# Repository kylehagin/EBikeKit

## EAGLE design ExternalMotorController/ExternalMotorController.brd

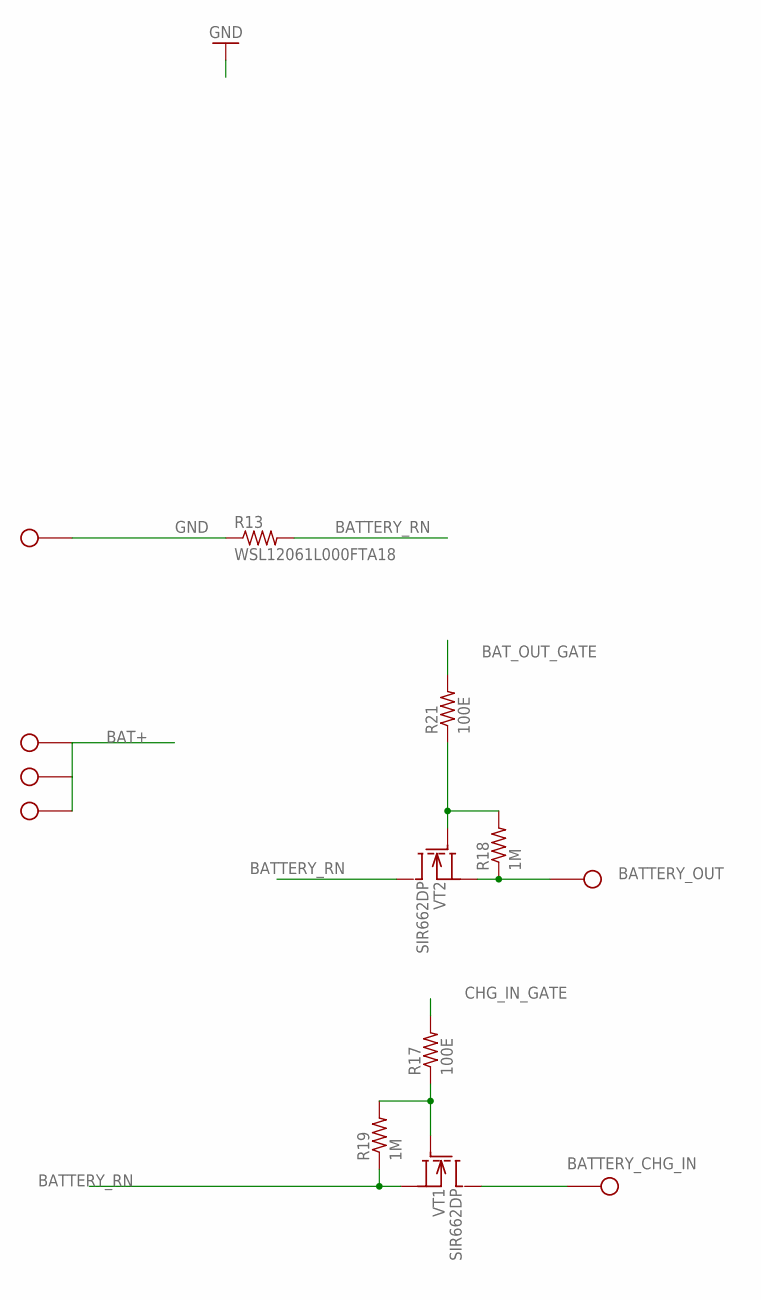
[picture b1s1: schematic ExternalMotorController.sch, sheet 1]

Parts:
R13: WSL12061L000FTA18; R2512
R17, R21: 100E; R0402
R18, R19: 1M; R0402
VT1, VT2: SIR662DP; POWERPAK_SO8
X1, X2, X3, X4, X5, X13: SOLDER_HOLE18AWG; SOLDER_HOLE_18

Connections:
BAT+: X1.1, X4.1, X5.1; also elsewhere on the board
BATTERY_CHG_IN: VT1.D, X2.1
BATTERY_OUT: R18.1, VT2.S1 (S), VT2.S2 (S), VT2.S3 (S), X3.1; also elsewhere on the board
BATTERY_RN: R13.2, R19.1, VT1.S1 (S), VT1.S2 (S), VT1.S3 (S), VT2.D; also elsewhere on the board
BAT_OUT_GATE: R21.2; also elsewhere on the board
CHG_IN_GATE: R17.2; also elsewhere on the board
GND: R13.1, X13.1; also elsewhere on the board
unnamed: R18.2, R21.1, VT2.G
unnamed: R17.1, R19.2, VT1.G

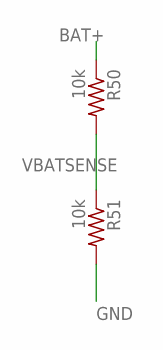
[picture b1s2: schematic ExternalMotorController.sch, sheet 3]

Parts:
R50, R51: 10k; R0402

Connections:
BAT+: R50.1; also elsewhere on the board
GND: R51.2; also elsewhere on the board
VBATSENSE: R50.2, R51.1; also elsewhere on the board

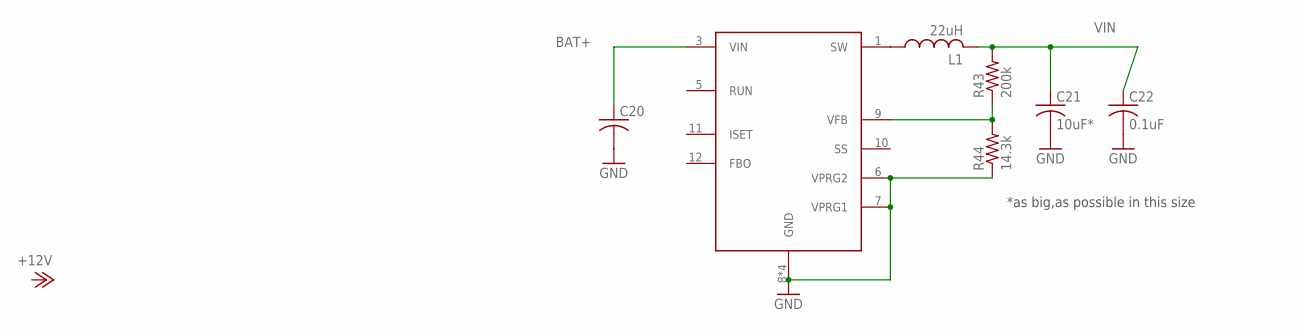
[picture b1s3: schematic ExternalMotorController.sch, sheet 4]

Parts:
C20: RCL_C-USC0805; RCL_C0805$1
C21: 10uF*; RCL_C4532$1
C22: 0.1uF; C0402
DA2: LTC3630; MSE16(12)
L1: 22uH; M-PAD-2.1_1210
R43: 200k; RCL_R0402
R44: 14.3k; RCL_R0402

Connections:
BAT+: C20.1, DA2.3 (VIN); also elsewhere on the board
GND: C20.2, C21.2, C22.2, DA2.6 (VPRG2), DA2.7 (VPRG1), DA2.8 (GND), DA2.14 (GND), DA2.16 (GND), DA2.17 (GND), R44.1; also elsewhere on the board
unnamed: DA2.1 (SW), L1.1
unnamed: DA2.9 (VFB), R43.1, R44.2
VIN: C21.1, C22.1, L1.2, R43.2; also elsewhere on the board

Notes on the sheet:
*as big,as possible in this size

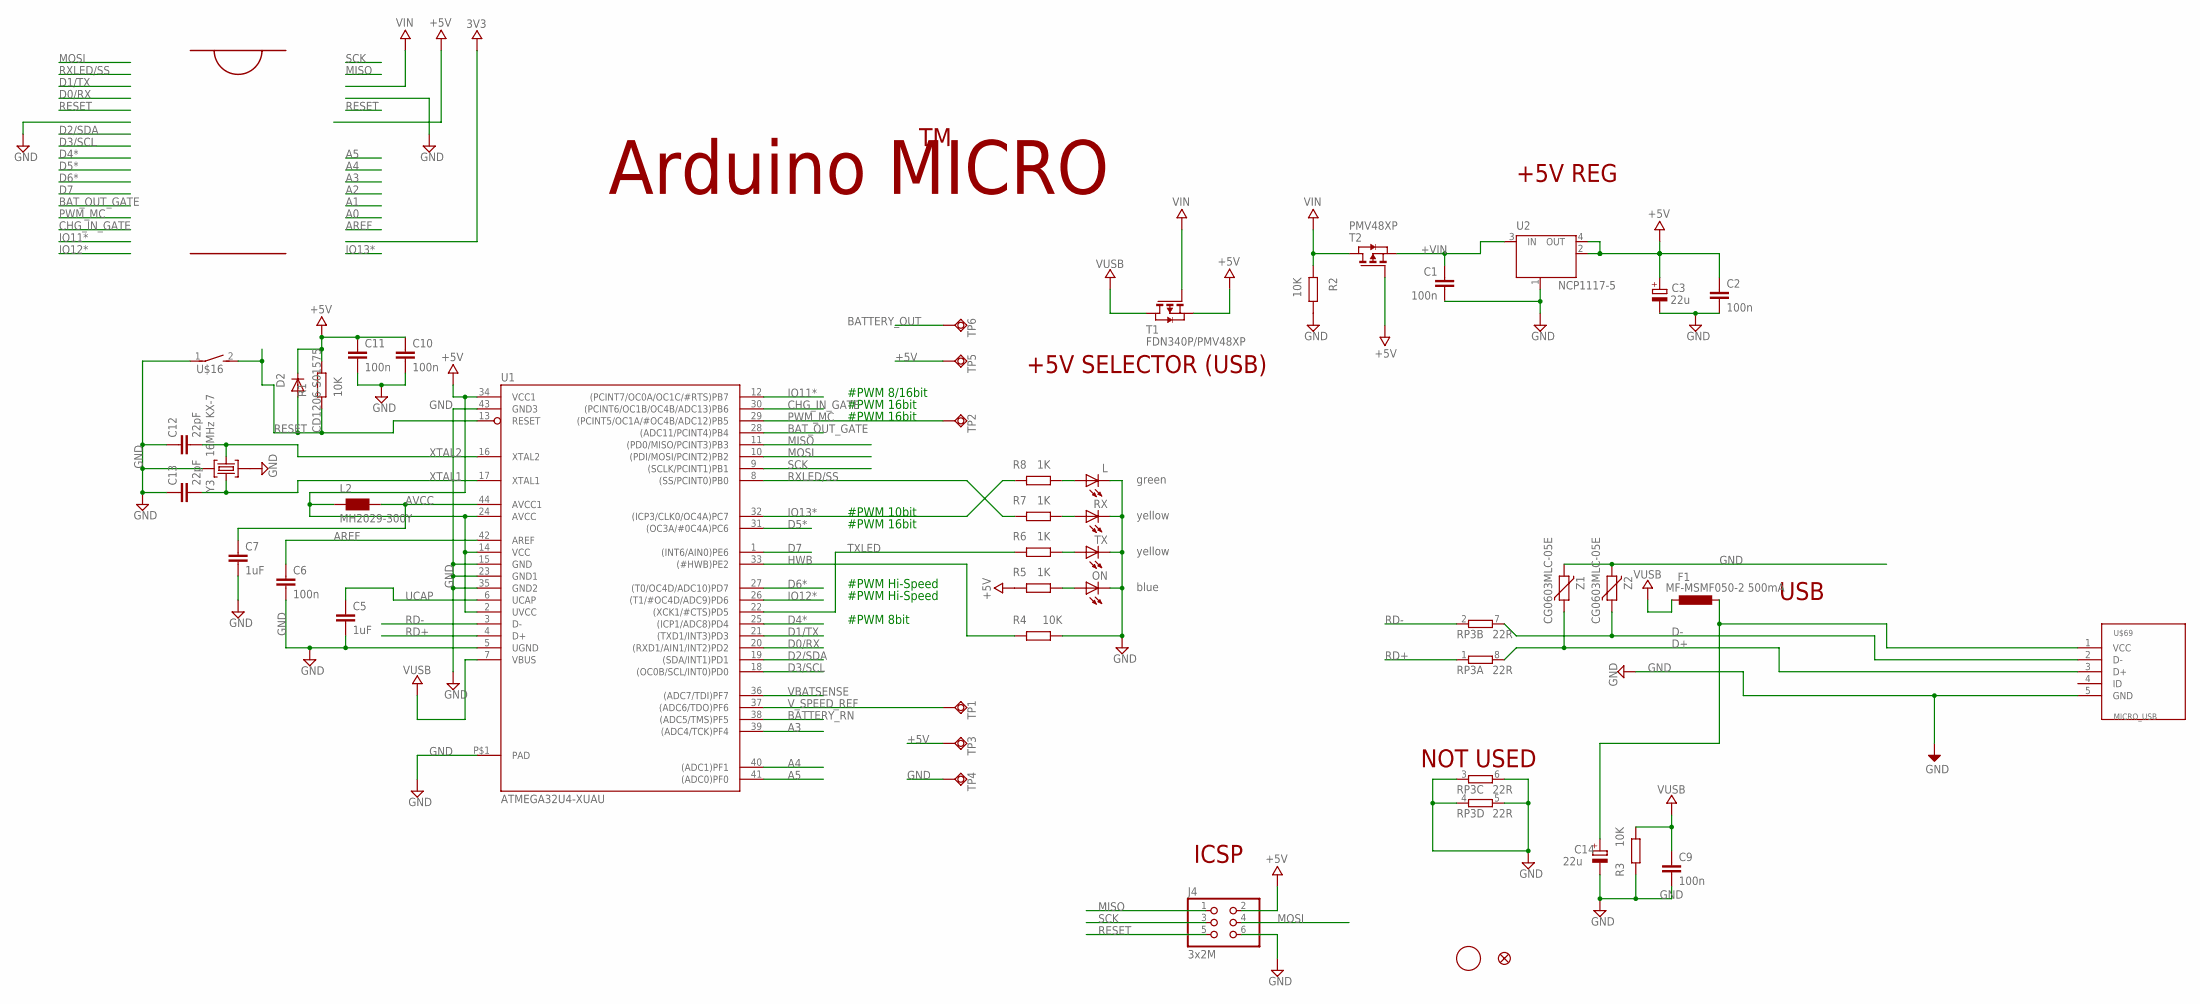
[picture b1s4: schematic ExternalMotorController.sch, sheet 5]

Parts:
C1, C2, C6, C9, C10, C11: 100n; C0402
C3, C14: 22u; SMC_B
C5, C7: 1uF; C0402
C12, C13: 22pF; C0402
D2: CD1206-S01575; MINIMELF
F1: MF-MSMF050-2 500mA; L1812
J4: 3x2M; 2X03
L: green; CHIPLED_0805
L2: MH2029-300Y; 0805
ON: blue; CHIPLED_0805
R1, R2, R3, R4: 10K; R0402
R5, R6, R7, R8: 1K; R0402
RP3: 22R; CAY16
RX: yellow; CHIPLED_0805
T1: FDN340P/PMV48XP; SOT-23
T2: PMV48XP; SOT-23
TP1, TP2, TP3, TP4, TP5, TP6: TPSQTP15SQ; TP15SQ
TX: yellow; CHIPLED_0805
U1: ATMEGA32U4-XUAU; TQFP44-PAD
U2: NCP1117-5; LINEAR_SOT223
U$16: RGHT-ANGLE-SMT-SWITCH-688-SKRELF; 2.9X3.9X2.0
U$37: FIDUCIALMOUNT; FIDUCIA-MOUNT
U$53: FIDUCIAL1X2; FIDUCIAL-1X2
U$69: MICRO_USB
Y3: 16MHz KX-7; CRYSTAL-3.2-2.5
Z1, Z2: CG0603MLC-05E; CT/CN0603

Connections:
+5V: C2.1, C3.+, C10.1, C11.1, D2.C, J4.2, L2.1, R1.1, R5.1, T1.2 (S), T2.3 (G), TP3.TP, TP5.TP, U1.2 (UVCC), U1.14 (VCC), U1.24 (AVCC), U1.34 (VCC1), U2.2 (OUT), U2.4 (OUT)
+VIN: C1.1, T2.2 (S), U2.3 (IN)
A3: U1.39 ((ADC4/TCK)PF4)
A4: U1.40 ((ADC1)PF1)
A5: U1.41 ((ADC0)PF0)
AREF: C6.1, U1.42 (AREF)
AVCC: C7.1, L2.2, U1.44 (AVCC1)
BATTERY_OUT: TP6.TP; also elsewhere on the board
BATTERY_RN: U1.38 ((ADC5/TMS)PF5); also elsewhere on the board
BAT_OUT_GATE: U1.28 ((ADC11/PCINT4)PB4); also elsewhere on the board
CHG_IN_GATE: U1.30 ((PCINT6/OC1B/OC4B/ADC13)PB6); also elsewhere on the board
D0/RX: U1.20 ((RXD1/AIN1/INT2)PD2)
D1/TX: U1.21 ((TXD1/INT3)PD3)
D2/SDA: U1.19 ((SDA/INT1)PD1)
D3/SCL: U1.18 ((OC0B/SCL/INT0)PD0)
D4*: U1.25 ((ICP1/ADC8)PD4)
D5*: U1.31 ((OC3A/#0C4A)PC6)
D6*: U1.27 ((T0/OC4D/ADC10)PD7)
D7: U1.1 ((INT6/AIN0)PE6)
D+: RP3.8 (2), U$69.3 (D+), Z1.1
D-: RP3.7 (2), U$69.2 (D-), Z2.1
GND: C1.2, C2.2, C3.-, C5.2, C6.2, C7.2, C9.2, C10.2, C11.2, C12.1, C13.1, C14.-, J4.6, L.C, ON.C, R2.1, R3.1, R4.2, RP3.3 (1), RP3.4 (1), RP3.5 (2), RP3.6 (2), RX.C, TP4.TP, TX.C, U1.5 (UGND), U1.15 (GND), U1.23 (GND1), U1.35 (GND2), U1.43 (GND3), U1.P$1 (PAD), U2.1 (GND/ADJ), U$16.1, U$69.5 (GND), Y3.2 (GND), Y3.4 (GND), Z1.2, Z2.2; also elsewhere on the board
HWB: R4.1, U1.33 ((#HWB)PE2)
IO11*: U1.12 ((PCINT7/OC0A/OC1C/#RTS)PB7)
IO12*: U1.26 ((T1/#OC4D/ADC9)PD6)
IO13*: R8.1, U1.32 ((ICP3/CLK0/OC4A)PC7)
MISO: J4.1, U1.11 ((PD0/MISO/PCINT3)PB3)
MOSI: J4.4, U1.10 ((PDI/MOSI/PCINT2)PB2)
unnamed: R7.2, RX.A
unnamed: ON.A, R5.2
unnamed: R6.2, TX.A
unnamed: L.A, R8.2
PWM_MC: TP2.TP, U1.29 ((PCINT5/OC1A/#OC4B/ADC12)PB5)
RD+: RP3.1, U1.4 (D+)
RD-: RP3.2 (1), U1.3 (D-)
RESET: D2.A, J4.5, R1.2, U1.13 (RESET), U$16.2
RXLED/SS: R7.1, U1.8 ((SS/PCINT0)PB0)
SCK: J4.3, U1.9 ((SCLK/PCINT1)PB1)
TXLED: R6.1, U1.22 ((XCK1/#CTS)PD5)
UCAP: C5.1, U1.6 (UCAP)
VBATSENSE: U1.36 ((ADC7/TDI)PF7); also elsewhere on the board
VIN: R2.2, T1.3 (G), T2.1 (D); also elsewhere on the board
VUSB: C9.1, F1.2, R3.2, T1.1 (D), U1.7 (VBUS)
VUSBD: C14.+, F1.1, U$69.1 (VCC)
V_SPEED_REF: TP1.TP, U1.37 ((ADC6/TDO)PF6)
XTAL1: C13.2, U1.17 (XTAL1), Y3.3 (C2)
XTAL2: C12.2, U1.16 (XTAL2), Y3.1 (C1)

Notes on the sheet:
Arduino MICRO
+5V REG
ICSP
USB
+5V SELECTOR (USB)
NOT USED
#PWM 8bit
#PWM Hi-Speed
#PWM 16bit
#PWM 10bit
#PWM 8/16bit

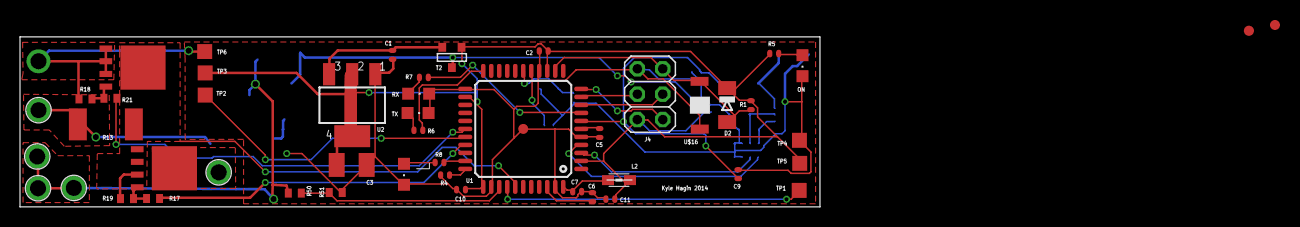
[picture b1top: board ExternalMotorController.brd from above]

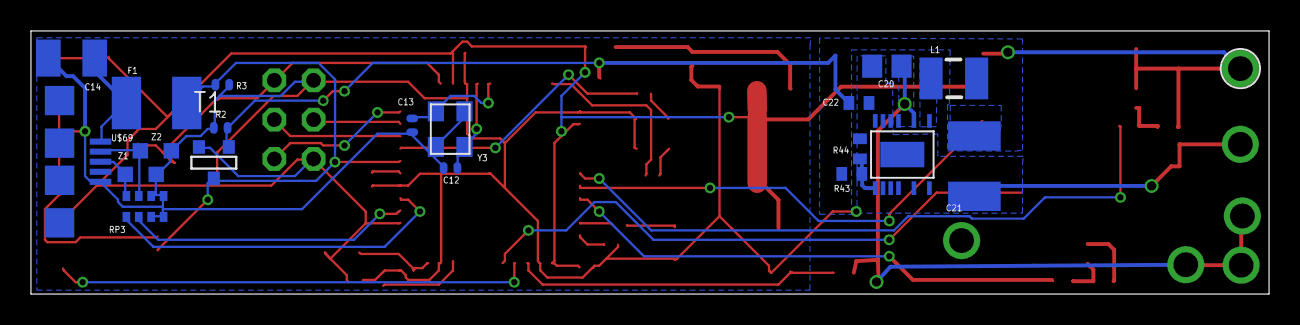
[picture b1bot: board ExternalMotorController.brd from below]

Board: 2 copper layers, 80.0 x 17.0 mm, 68 parts (20 on the bottom side), 40 nets.

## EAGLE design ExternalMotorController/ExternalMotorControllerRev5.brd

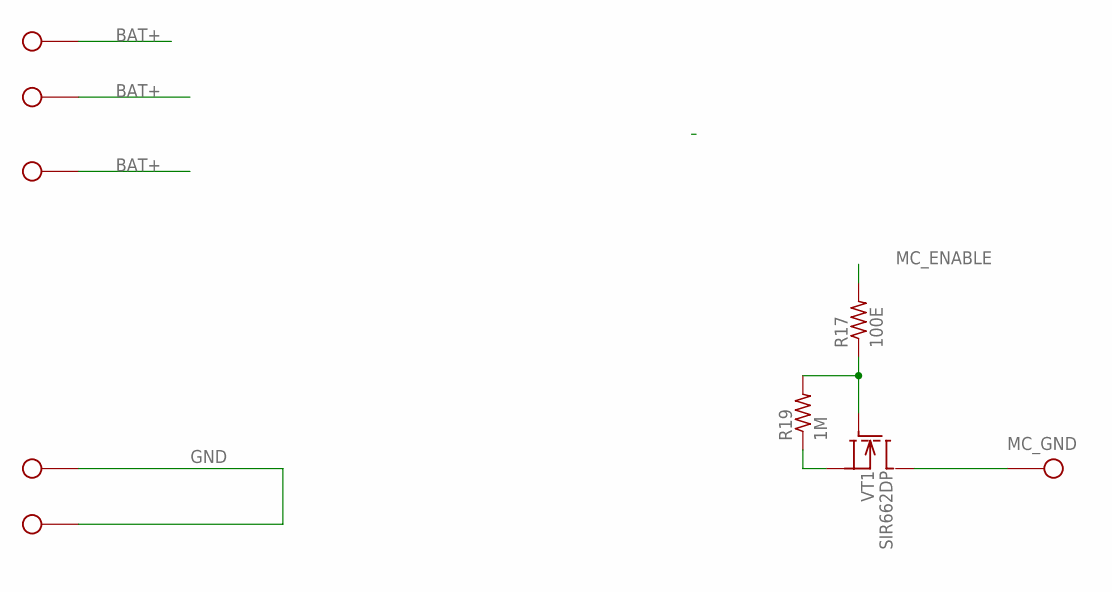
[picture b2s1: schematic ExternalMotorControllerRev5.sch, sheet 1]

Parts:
R17: 100E; R0402
R19: 1M; R0402
VT1: SIR662DP; POWERPAK_SO8
X1, X2, X3, X4, X5, X13: SOLDER_HOLE18AWG; SOLDER_HOLE_18

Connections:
BAT+: X1.1, X3.1, X4.1; also elsewhere on the board
GND: R19.1, VT1.S1 (S), VT1.S2 (S), VT1.S3 (S), X5.1, X13.1; also elsewhere on the board
MC_ENABLE: R17.2; also elsewhere on the board
MC_GND: VT1.D, X2.1; also elsewhere on the board
unnamed: R17.1, R19.2, VT1.G

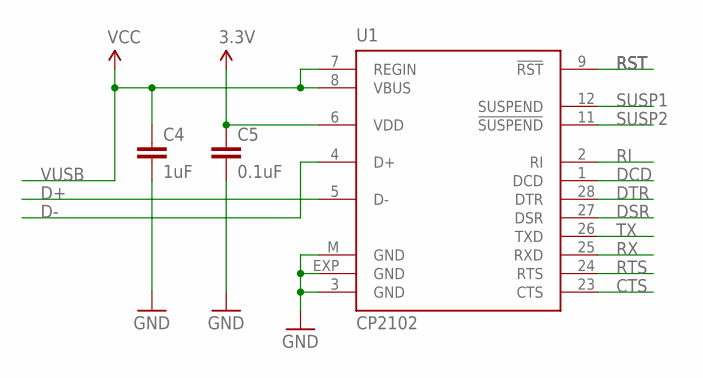
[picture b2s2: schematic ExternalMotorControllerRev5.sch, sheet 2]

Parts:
C4: 1uF; C0402
C5: 0.1uF; C0402
U1: CP2102; MLP28

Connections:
3.3V: C5.1, U1.6 (VDD)
CTS: U1.23 (CTS)
D+: U1.5 (D-)
D-: U1.4 (D+)
DCD: U1.1 (DCD)
DSR: U1.27 (DSR)
DTR: U1.28 (DTR); also elsewhere on the board
GND: C4.2, C5.2, U1.3 (GND), U1.EXP (GND), U1.M (GND); also elsewhere on the board
RI: U1.2 (RI)
RST: U1.9 (!RST)
RTS: U1.24 (RTS)
RX: U1.25 (RXD); also elsewhere on the board
SUSP1: U1.12 (SUSPEND)
SUSP2: U1.11 (!SUSPEND)
TX: U1.26 (TXD); also elsewhere on the board
VUSB: C4.1, U1.7 (REGIN), U1.8 (VBUS); also elsewhere on the board

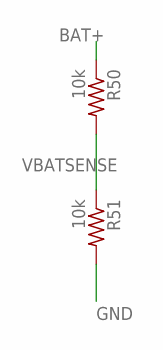
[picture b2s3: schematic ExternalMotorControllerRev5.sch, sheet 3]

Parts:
R50, R51: 10k; R0402

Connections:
BAT+: R50.1; also elsewhere on the board
GND: R51.2; also elsewhere on the board
VBATSENSE: R50.2, R51.1; also elsewhere on the board

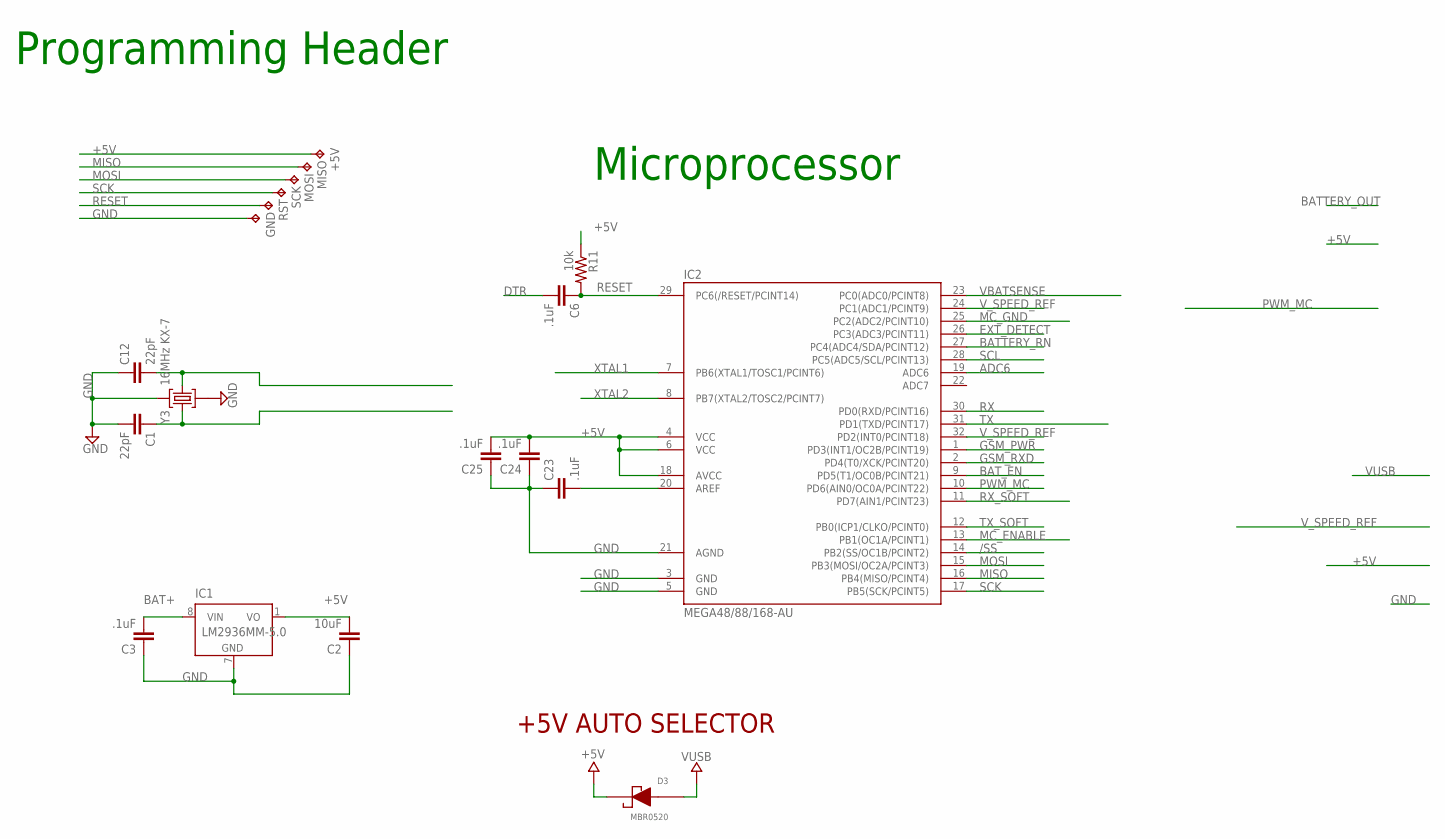
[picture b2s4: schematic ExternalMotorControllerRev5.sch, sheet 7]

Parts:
+5V: TPTP08R; TP08R
C1, C12: 22pF; C0402
C2: 10uF; C0805
C3, C6, C23, C24, C25: .1uF; C0402
D3: MBR0520; SOD-123
GND: TPTP10R; TP10R
IC1: LM2936MM-5.0; MINI-SO8
IC2: MEGA48/88/168-AU; TQFP32-08
MISO: TPTP08R; TP08R
MOSI: TPTP08R; TP08R
R11: 10k; R0402
RST: TPTP10R; TP10R
SCK: TPTP08R; TP08R
Y3: 16MHz KX-7; CRYSTAL-3.2-2.5

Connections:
+5V: +5V.TP, C2.2, C24.2, C25.2, D3.1 (CA), IC1.1 (VO), IC2.4 (VCC), IC2.6 (VCC), IC2.18 (AVCC), R11.1
/SS: IC2.14 (PB2(SS/OC1B/PCINT2))
ADC6: IC2.19 (ADC6)
BAT+: C3.2, IC1.8 (VIN); also elsewhere on the board
BATTERY_RN: IC2.27 (PC4(ADC4/SDA/PCINT12))
BAT_EN: IC2.9 (PD5(T1/OC0B/PCINT21))
DTR: C6.2; also elsewhere on the board
EXT_DETECT: IC2.26 (PC3(ADC3/PCINT11))
GND: C1.2, C2.1, C3.1, C12.1, C23.1, C24.1, C25.1, GND.TP, IC1.7 (GND), IC2.3 (GND), IC2.5 (GND), IC2.21 (AGND), Y3.2 (GND), Y3.4 (GND); also elsewhere on the board
GSM_PWR: IC2.1 (PD3(INT1/OC2B/PCINT19))
GSM_RXD: IC2.2 (PD4(T0/XCK/PCINT20))
MC_ENABLE: IC2.13 (PB1(OC1A/PCINT1)); also elsewhere on the board
MC_GND: IC2.25 (PC2(ADC2/PCINT10)); also elsewhere on the board
MISO: IC2.16 (PB4(MISO/PCINT4)), MISO.TP
MOSI: IC2.15 (PB3(MOSI/OC2A/PCINT3)), MOSI.TP
unnamed: C23.2, IC2.20 (AREF)
PWM_MC: IC2.10 (PD6(AIN0/OC0A/PCINT22))
RESET: C6.1, IC2.29 (PC6(/RESET/PCINT14)), R11.2, RST.TP
RX: IC2.30 (PD0(RXD/PCINT16)); also elsewhere on the board
RX_SOFT: IC2.11 (PD7(AIN1/PCINT23))
SCK: IC2.17 (PB5(SCK/PCINT5)), SCK.TP
SCL: IC2.28 (PC5(ADC5/SCL/PCINT13))
TX: IC2.31 (PD1(TXD/PCINT17)); also elsewhere on the board
TX_SOFT: IC2.12 (PB0(ICP1/CLKO/PCINT0))
VBATSENSE: IC2.23 (PC0(ADC0/PCINT8)); also elsewhere on the board
VUSB: D3.2 (AN); also elsewhere on the board
V_SPEED_REF: IC2.24 (PC1(ADC1/PCINT9)), IC2.32 (PD2(INT0/PCINT18))
XTAL1: C12.2, IC2.7 (PB6(XTAL1/TOSC1/PCINT6)), Y3.1 (C1)
XTAL2: C1.1, IC2.8 (PB7(XTAL2/TOSC2/PCINT7)), Y3.3 (C2)

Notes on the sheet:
Microprocessor
Programming Header
+5V AUTO SELECTOR

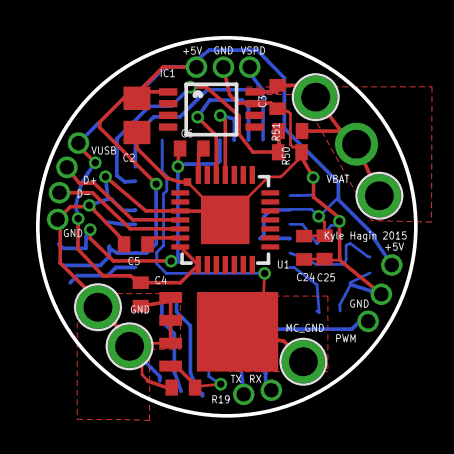
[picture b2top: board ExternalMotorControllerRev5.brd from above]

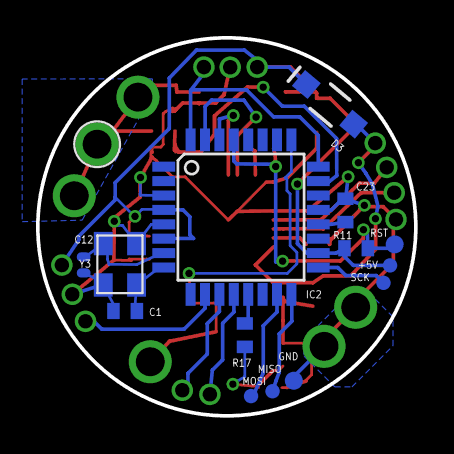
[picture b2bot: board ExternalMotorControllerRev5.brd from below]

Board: 2 copper layers, 21.0 x 21.0 mm, 33 parts (15 on the bottom side), 20 nets.

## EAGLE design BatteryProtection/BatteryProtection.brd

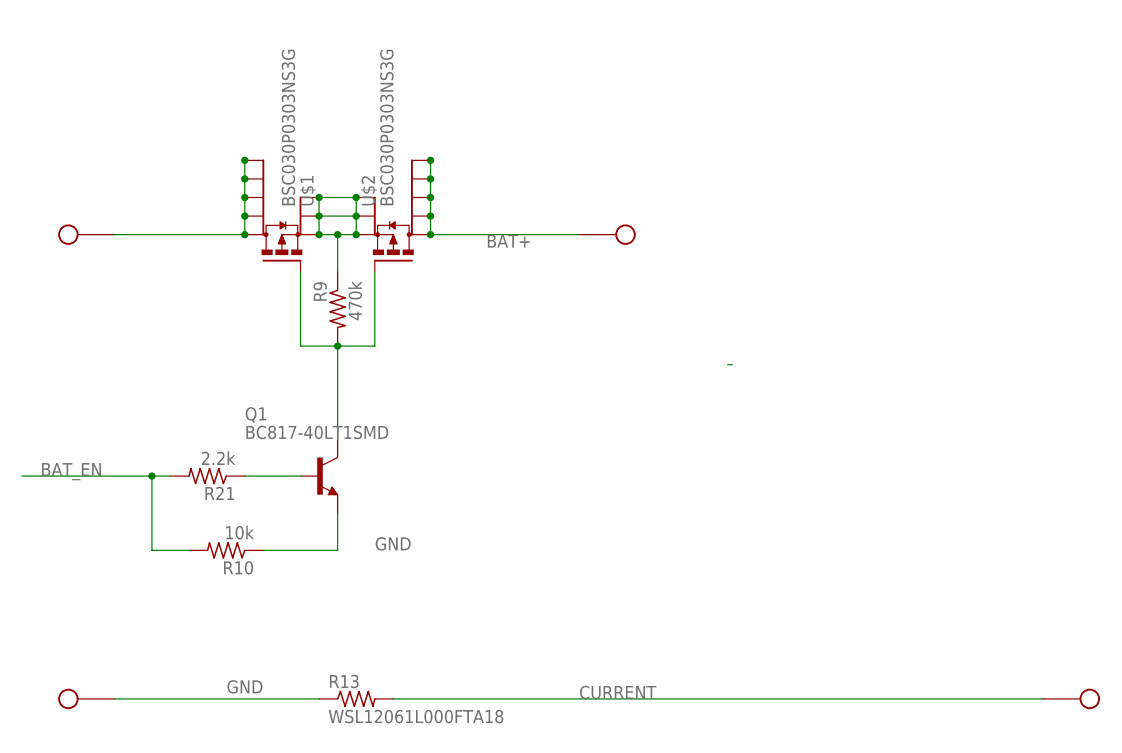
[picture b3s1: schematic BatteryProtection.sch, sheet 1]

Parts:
Q1: BC817-40LT1SMD; SOT23-BEC
R9: 470k; R0402
R10: 10k; R0402
R13: WSL12061L000FTA18; R2512
R21: 2.2k; R0402
U$1, U$2: BSC030P0303NS3G; PG-TDSON-8
X1, X2, X5, X13: SOLDER_HOLE18AWG; SOLDER_HOLE_18

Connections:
BAT+: U$2.5 (D), U$2.6 (D1), U$2.7 (D2), U$2.8 (D3), U$2.TH (D4), X1.1; also elsewhere on the board
BAT_EN: R10.2, R21.2; also elsewhere on the board
CURRENT: R13.2, X2.1; also elsewhere on the board
GND: Q1.E, R10.1, R13.1, X13.1; also elsewhere on the board
unnamed: R9.1, U$1.1 (S), U$1.2 (S1), U$1.3 (S2), U$2.1 (S), U$2.2 (S1), U$2.3 (S2)
unnamed: Q1.B, R21.1
unnamed: Q1.C, R9.2, U$1.4 (G), U$2.4 (G)
unnamed: U$1.5 (D), U$1.6 (D1), U$1.7 (D2), U$1.8 (D3), U$1.TH (D4), X5.1

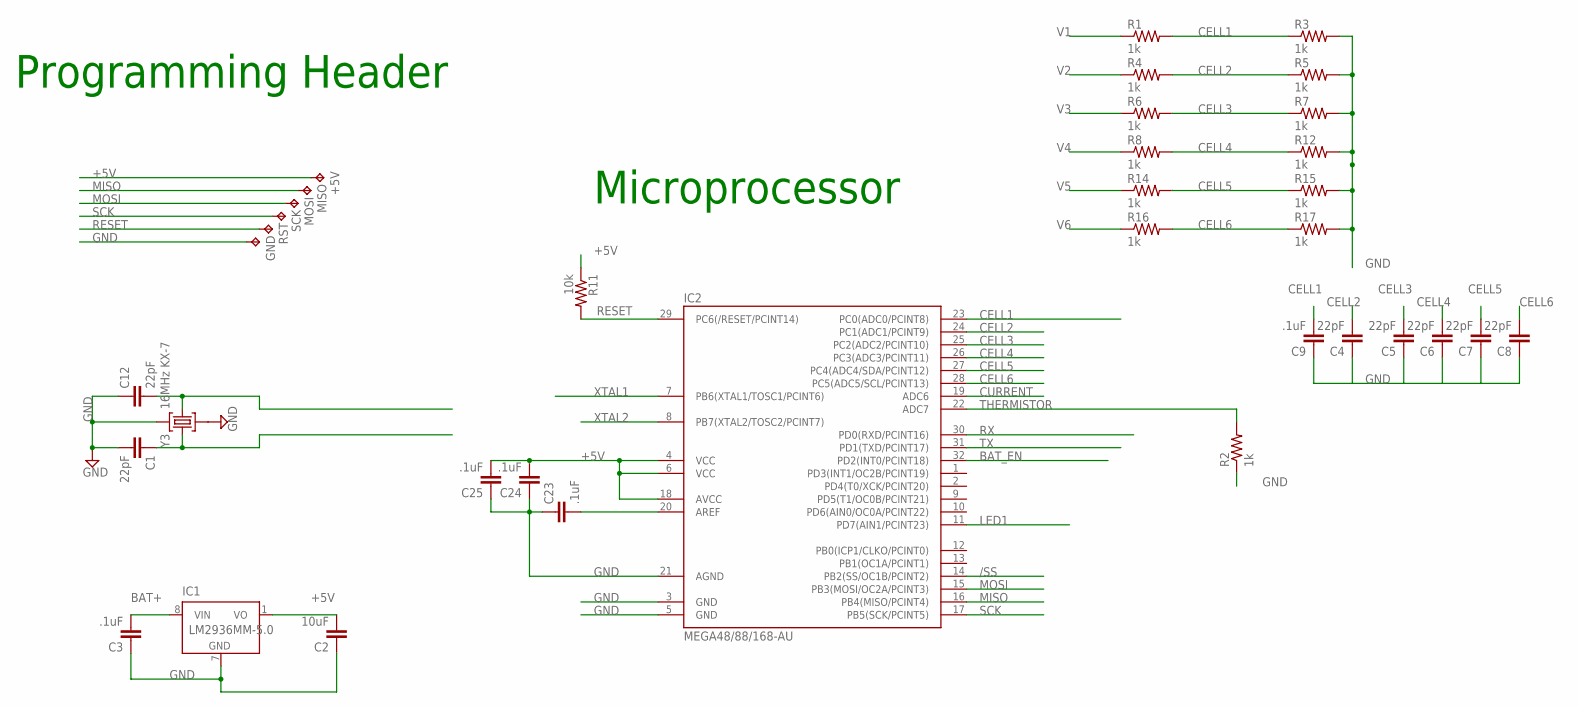
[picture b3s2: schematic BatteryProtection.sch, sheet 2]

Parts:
+5V: TPTP08R; TP08R
C1, C4, C5, C6, C7, C8, C12: 22pF; C0402
C2: 10uF; C0805
C3, C9, C23, C24, C25: .1uF; C0402
GND: TPTP08R; TP08R
IC1: LM2936MM-5.0; MINI-SO8
IC2: MEGA48/88/168-AU; TQFP32-08
MISO: TPTP08R; TP08R
MOSI: TPTP08R; TP08R
R1, R2, R3, R4, R5, R6, R7, R8, R12, R14, R15, R16, R17: 1k; R0402
R11: 10k; R0402
RST: TPTP08R; TP08R
SCK: TPTP08R; TP08R
Y3: 16MHz KX-7; CRYSTAL-3.2-2.5

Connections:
+5V: +5V.TP, C2.2, C24.2, C25.2, IC1.1 (VO), IC2.4 (VCC), IC2.6 (VCC), IC2.18 (AVCC), R11.1
/SS: IC2.14 (PB2(SS/OC1B/PCINT2))
BAT+: C3.2, IC1.8 (VIN); also elsewhere on the board
BAT_EN: IC2.32 (PD2(INT0/PCINT18)); also elsewhere on the board
CELL1: C9.2, IC2.23 (PC0(ADC0/PCINT8)), R1.2, R3.1
CELL2: C4.2, IC2.24 (PC1(ADC1/PCINT9)), R4.2, R5.1
CELL3: C5.2, IC2.25 (PC2(ADC2/PCINT10)), R6.2, R7.1
CELL4: C6.2, IC2.26 (PC3(ADC3/PCINT11)), R8.2, R12.1
CELL5: C7.2, IC2.27 (PC4(ADC4/SDA/PCINT12)), R14.2, R15.1
CELL6: C8.2, IC2.28 (PC5(ADC5/SCL/PCINT13)), R16.2, R17.1
CURRENT: IC2.19 (ADC6); also elsewhere on the board
GND: C1.2, C2.1, C3.1, C4.1, C5.1, C6.1, C7.1, C8.1, C9.1, C12.1, C23.1, C24.1, C25.1, GND.TP, IC1.7 (GND), IC2.3 (GND), IC2.5 (GND), IC2.21 (AGND), R2.1, R3.2, R5.2, R7.2, R12.2, R15.2, R17.2, Y3.2 (GND), Y3.4 (GND); also elsewhere on the board
LED1: IC2.11 (PD7(AIN1/PCINT23))
MISO: IC2.16 (PB4(MISO/PCINT4)), MISO.TP
MOSI: IC2.15 (PB3(MOSI/OC2A/PCINT3)), MOSI.TP
unnamed: C23.2, IC2.20 (AREF)
RESET: IC2.29 (PC6(/RESET/PCINT14)), R11.2, RST.TP
RX: IC2.30 (PD0(RXD/PCINT16))
SCK: IC2.17 (PB5(SCK/PCINT5)), SCK.TP
THERMISTOR: IC2.22 (ADC7), R2.2
TX: IC2.31 (PD1(TXD/PCINT17))
V1: R1.1
V2: R4.1
V3: R6.1
V4: R8.1
V5: R14.1
V6: R16.1
XTAL1: C1.1, IC2.7 (PB6(XTAL1/TOSC1/PCINT6)), Y3.3 (C2)
XTAL2: C12.2, IC2.8 (PB7(XTAL2/TOSC2/PCINT7)), Y3.1 (C1)

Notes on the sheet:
Microprocessor
Programming Header

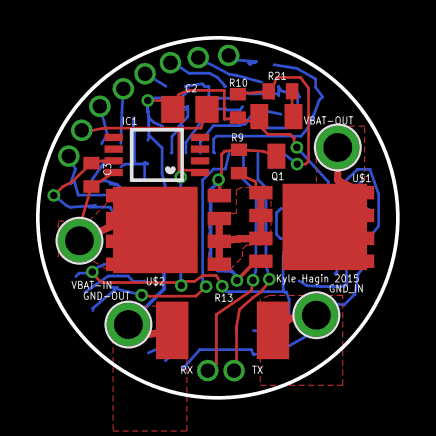
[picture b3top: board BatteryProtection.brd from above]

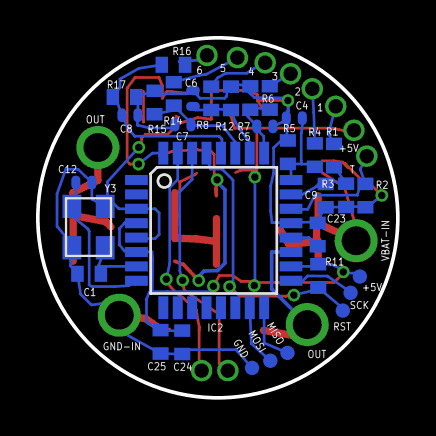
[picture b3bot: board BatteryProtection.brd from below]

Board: 2 copper layers, 20.0 x 20.0 mm, 47 parts (33 on the bottom side), 23 nets.

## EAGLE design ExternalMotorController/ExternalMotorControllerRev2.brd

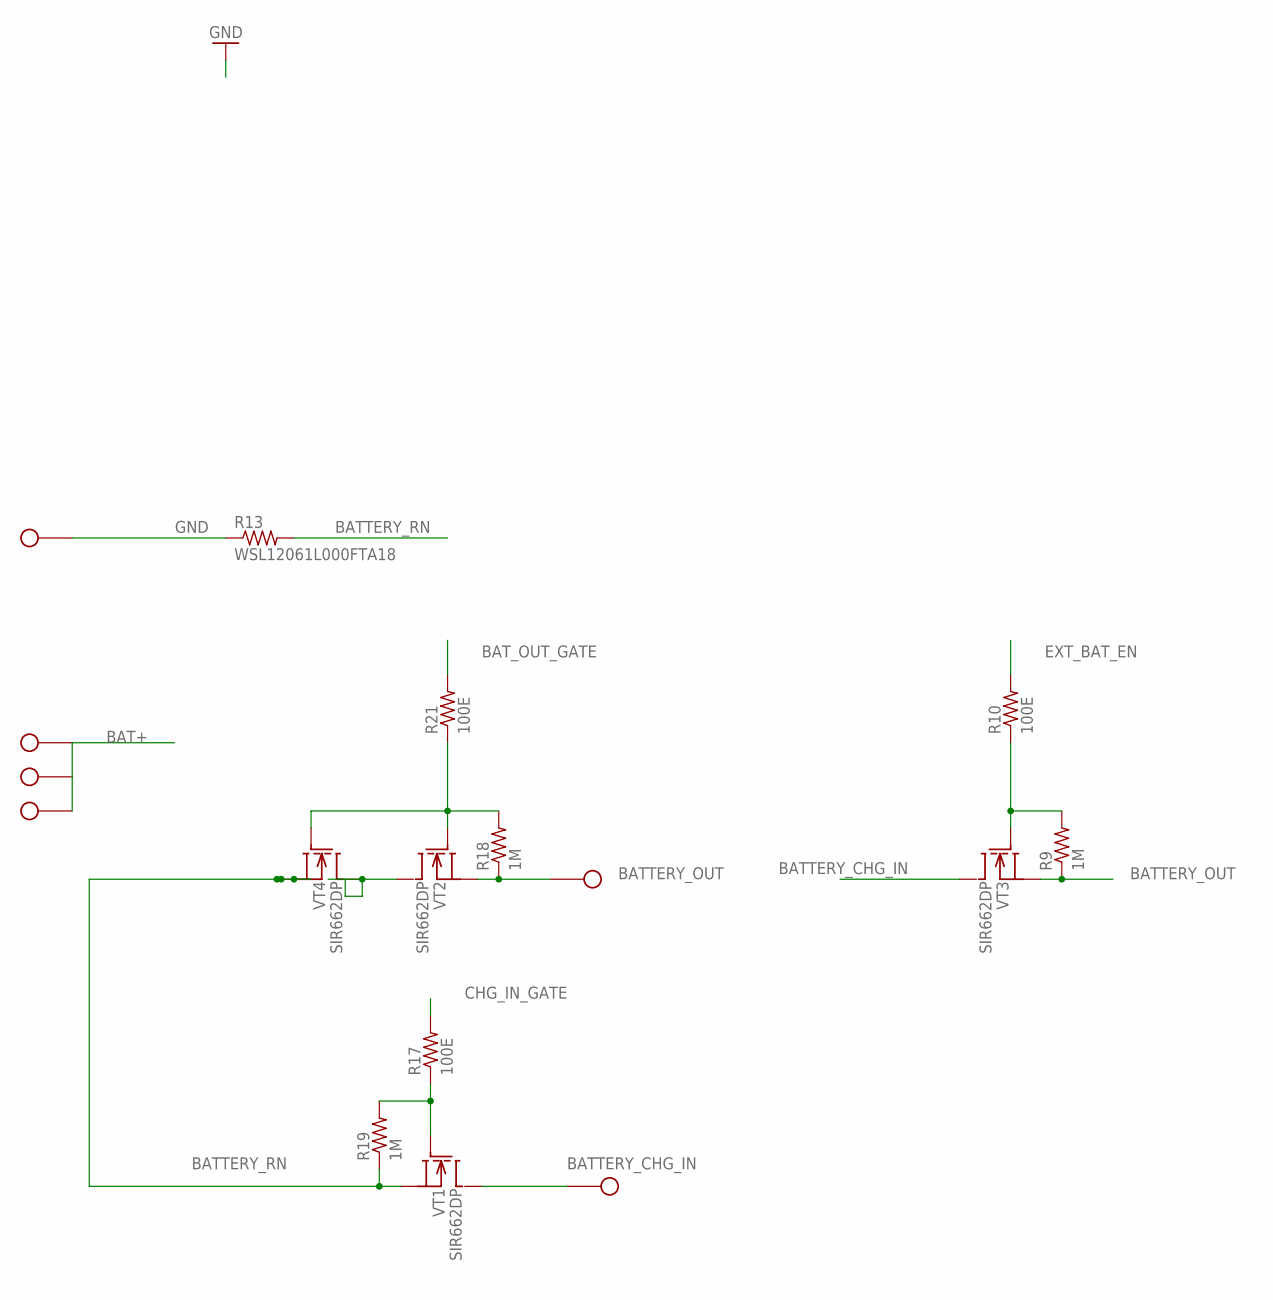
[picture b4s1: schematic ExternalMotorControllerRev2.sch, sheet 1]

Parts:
R9, R18, R19: 1M; R0402
R10, R17, R21: 100E; R0402
R13: WSL12061L000FTA18; R2512
VT1, VT2, VT3, VT4: SIR662DP; POWERPAK_SO8
X1, X2, X3, X4, X5, X13: SOLDER_HOLE18AWG; SOLDER_HOLE_18

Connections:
BAT+: X1.1, X4.1, X5.1; also elsewhere on the board
BATTERY_CHG_IN: VT1.D, VT3.D, X2.1
BATTERY_OUT: R9.1, R18.1, VT2.S1 (S), VT2.S2 (S), VT2.S3 (S), VT3.S1 (S), VT3.S2 (S), VT3.S3 (S), X3.1; also elsewhere on the board
BATTERY_RN: R13.2, R19.1, VT1.S1 (S), VT1.S2 (S), VT1.S3 (S), VT4.S1 (S), VT4.S2 (S), VT4.S3 (S); also elsewhere on the board
BAT_OUT_GATE: R21.2; also elsewhere on the board
CHG_IN_GATE: R17.2; also elsewhere on the board
EXT_BAT_EN: R10.2; also elsewhere on the board
GND: R13.1, X13.1; also elsewhere on the board
unnamed: R9.2, R10.1, VT3.G
unnamed: VT2.D, VT4.D
unnamed: R18.2, R21.1, VT2.G, VT4.G
unnamed: R17.1, R19.2, VT1.G

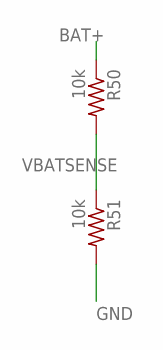
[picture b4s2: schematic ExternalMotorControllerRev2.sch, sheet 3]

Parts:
R50, R51: 10k; R0402

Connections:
BAT+: R50.1; also elsewhere on the board
GND: R51.2; also elsewhere on the board
VBATSENSE: R50.2, R51.1; also elsewhere on the board

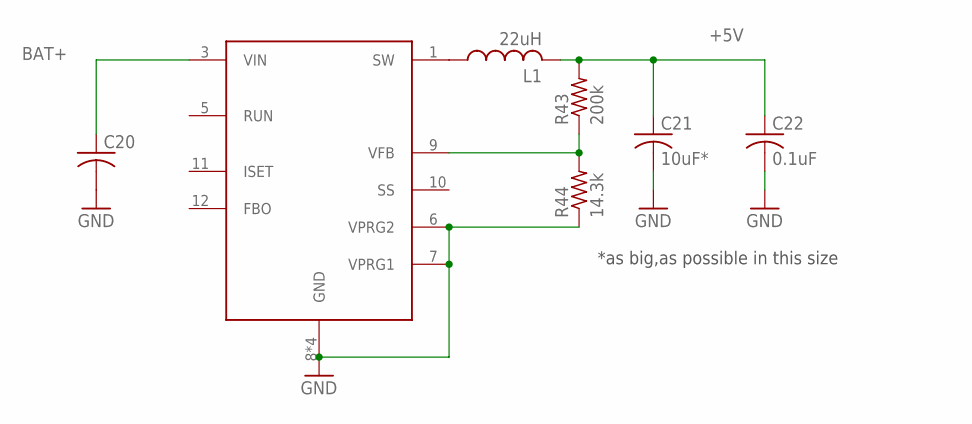
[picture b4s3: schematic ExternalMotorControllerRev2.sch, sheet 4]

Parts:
C20: RCL_C-USC0805; RCL_C0805$1
C21: 10uF*; RCL_C4532$1
C22: 0.1uF; C0402
DA2: LTC3630; MSE16(12)
L1: 22uH; M-PAD-2.1_1210
R43: 200k; RCL_R0402
R44: 14.3k; RCL_R0402

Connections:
+5V: C21.1, C22.1, L1.2, R43.2; also elsewhere on the board
BAT+: C20.1, DA2.3 (VIN); also elsewhere on the board
GND: C20.2, C21.2, C22.2, DA2.6 (VPRG2), DA2.7 (VPRG1), DA2.8 (GND), DA2.14 (GND), DA2.16 (GND), DA2.17 (GND), R44.1; also elsewhere on the board
unnamed: DA2.1 (SW), L1.1
unnamed: DA2.9 (VFB), R43.1, R44.2

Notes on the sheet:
*as big,as possible in this size

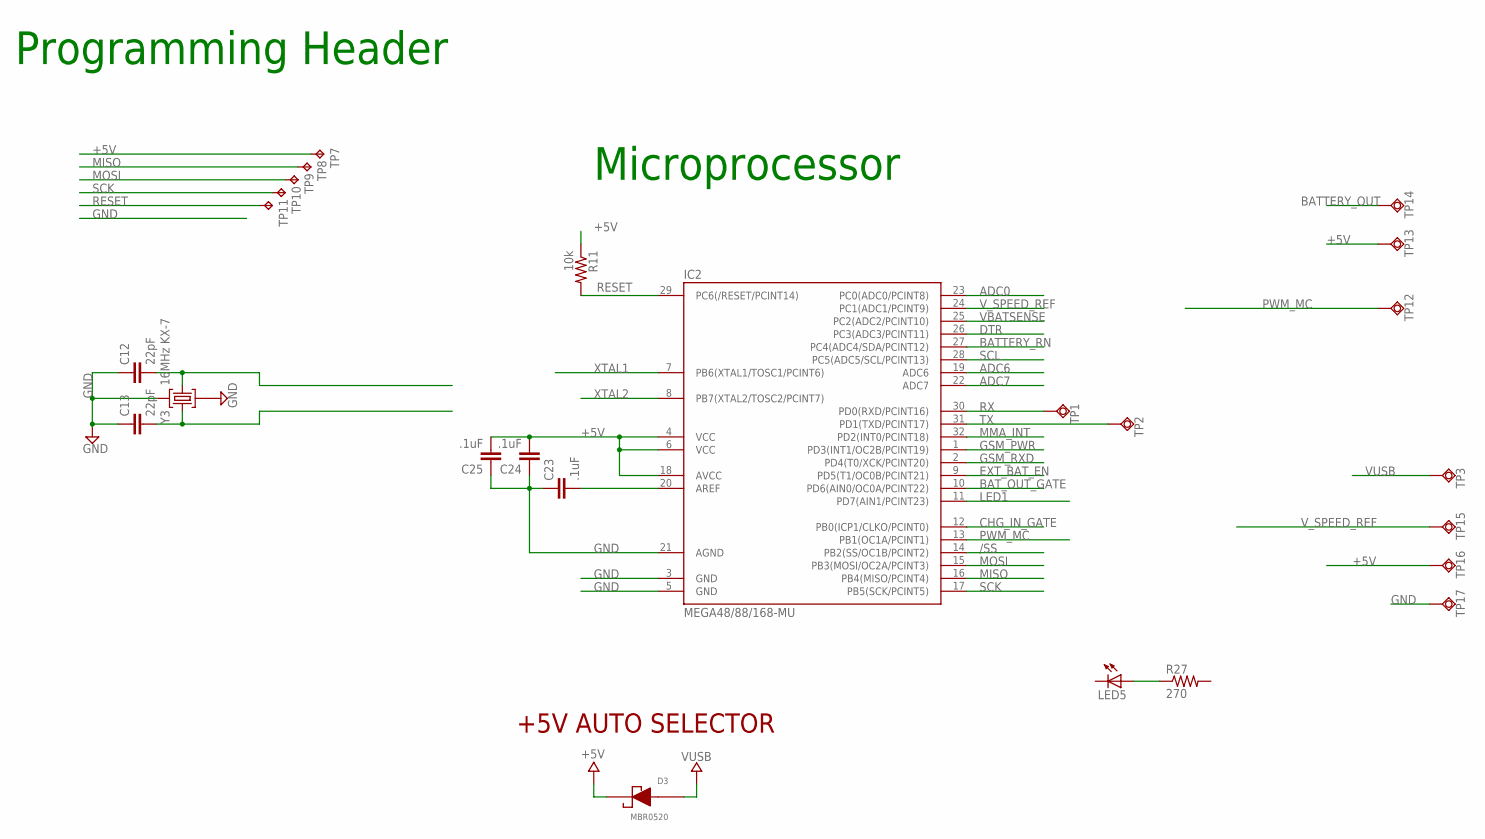
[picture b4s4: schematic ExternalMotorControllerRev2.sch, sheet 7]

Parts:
C12, C13: 22pF; C0402
C23, C24, C25: .1uF; C0402
D3: MBR0520; SOD-123
IC2: MEGA48/88/168-MU; MLF32
LED5: LEDCHIP-LED0603; CHIP-LED0603
R11: 10k; R0402
R27: 270; R0402
TP1, TP2, TP3, TP15: TPSQTP15R; TP15R
TP7, TP8, TP9, TP10: TPTP08R; TP08R
TP11: TPTP10R; TP10R
TP12, TP13, TP14, TP16, TP17: TPSQTP15SQ; TP15SQ
Y3: 16MHz KX-7; CRYSTAL-3.2-2.5

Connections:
+5V: C24.2, C25.2, D3.1 (CA), IC2.4 (VCC), IC2.6 (VCC), IC2.18 (AVCC), R11.1, TP7.TP, TP13.TP, TP16.TP; also elsewhere on the board
/SS: IC2.14 (PB2(SS/OC1B/PCINT2))
ADC0: IC2.23 (PC0(ADC0/PCINT8))
ADC6: IC2.19 (ADC6)
ADC7: IC2.22 (ADC7)
BATTERY_OUT: TP14.TP; also elsewhere on the board
BATTERY_RN: IC2.27 (PC4(ADC4/SDA/PCINT12)); also elsewhere on the board
BAT_OUT_GATE: IC2.10 (PD6(AIN0/OC0A/PCINT22)); also elsewhere on the board
CHG_IN_GATE: IC2.12 (PB0(ICP1/CLKO/PCINT0)); also elsewhere on the board
DTR: IC2.26 (PC3(ADC3/PCINT11))
EXT_BAT_EN: IC2.9 (PD5(T1/OC0B/PCINT21)); also elsewhere on the board
GND: C12.1, C13.1, C23.1, C24.1, C25.1, IC2.3 (GND), IC2.5 (GND), IC2.21 (AGND), TP17.TP, Y3.2 (GND), Y3.4 (GND); also elsewhere on the board
GSM_PWR: IC2.1 (PD3(INT1/OC2B/PCINT19))
GSM_RXD: IC2.2 (PD4(T0/XCK/PCINT20))
LED1: IC2.11 (PD7(AIN1/PCINT23))
MISO: IC2.16 (PB4(MISO/PCINT4)), TP8.TP
MMA_INT: IC2.32 (PD2(INT0/PCINT18))
MOSI: IC2.15 (PB3(MOSI/OC2A/PCINT3)), TP9.TP
unnamed: C23.2, IC2.20 (AREF)
unnamed: LED5.A, R27.1
PWM_MC: IC2.13 (PB1(OC1A/PCINT1)), TP12.TP
RESET: IC2.29 (PC6(/RESET/PCINT14)), R11.2, TP11.TP
RX: IC2.30 (PD0(RXD/PCINT16)), TP1.TP
SCK: IC2.17 (PB5(SCK/PCINT5)), TP10.TP
SCL: IC2.28 (PC5(ADC5/SCL/PCINT13))
TX: IC2.31 (PD1(TXD/PCINT17)), TP2.TP
VBATSENSE: IC2.25 (PC2(ADC2/PCINT10)); also elsewhere on the board
VUSB: D3.2 (AN), TP3.TP
V_SPEED_REF: IC2.24 (PC1(ADC1/PCINT9)), TP15.TP
XTAL1: C13.2, IC2.7 (PB6(XTAL1/TOSC1/PCINT6)), Y3.3 (C2)
XTAL2: C12.2, IC2.8 (PB7(XTAL2/TOSC2/PCINT7)), Y3.1 (C1)

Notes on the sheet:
Microprocessor
Programming Header
+5V AUTO SELECTOR
